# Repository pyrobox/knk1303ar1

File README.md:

# KNK1303AR1

Project of firing module of amateur pyrotechnic system. 

## Description

For many years, the forum of fireworks enthusiasts https://forumfajerwerki.pl has been implementing projects of amateur pyrotechnic systems. 
KNK1303AR1 is another project, this time compatible with the professional Pyrobox pirotechnics system, based on the Arduino Nano Every board.
The design of the pcb was created in KiCad 7.0.8 and the code for Arduino Nano Every was written in Arduino IDE 2.3.2
This module is controlled by the free Pyrobox system software downloadable from https://www.pyrobox.com.pl/soft/downloads.html

## Help

You can find more information on the forumfajerwerki.pl in the thread 
https://www.forumfajerwerki.pl/topic/9585-forumowy-projekt-opensource-systemu-pirotechnicznego/?do=findComment&comment=165880 
Forum registration is required.

A compendium of projects from the forumfajerwerki.pl
https://www.pyrobox.com.pl/knk1301/

## Authors

Zbigniew Kubicki (forumfajerwerki.pl nickname "zk1959")

## Version History

* Rev.1 as of 2024.03.10

## License

Open source hardware and freeware software.

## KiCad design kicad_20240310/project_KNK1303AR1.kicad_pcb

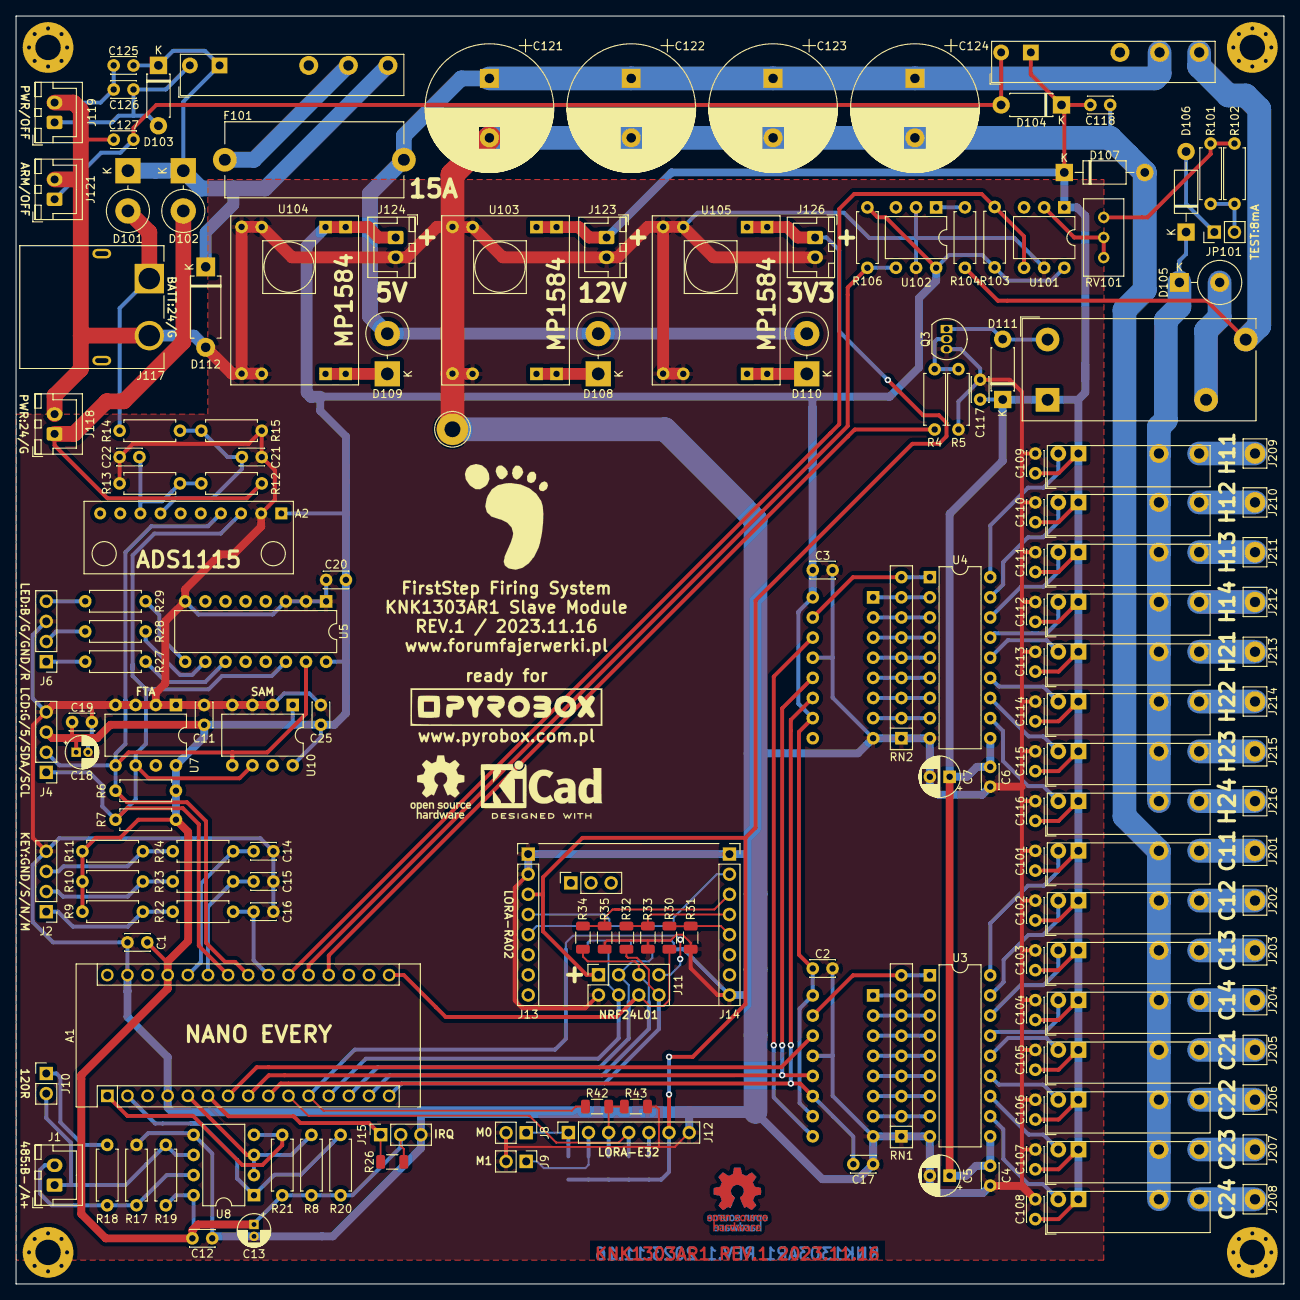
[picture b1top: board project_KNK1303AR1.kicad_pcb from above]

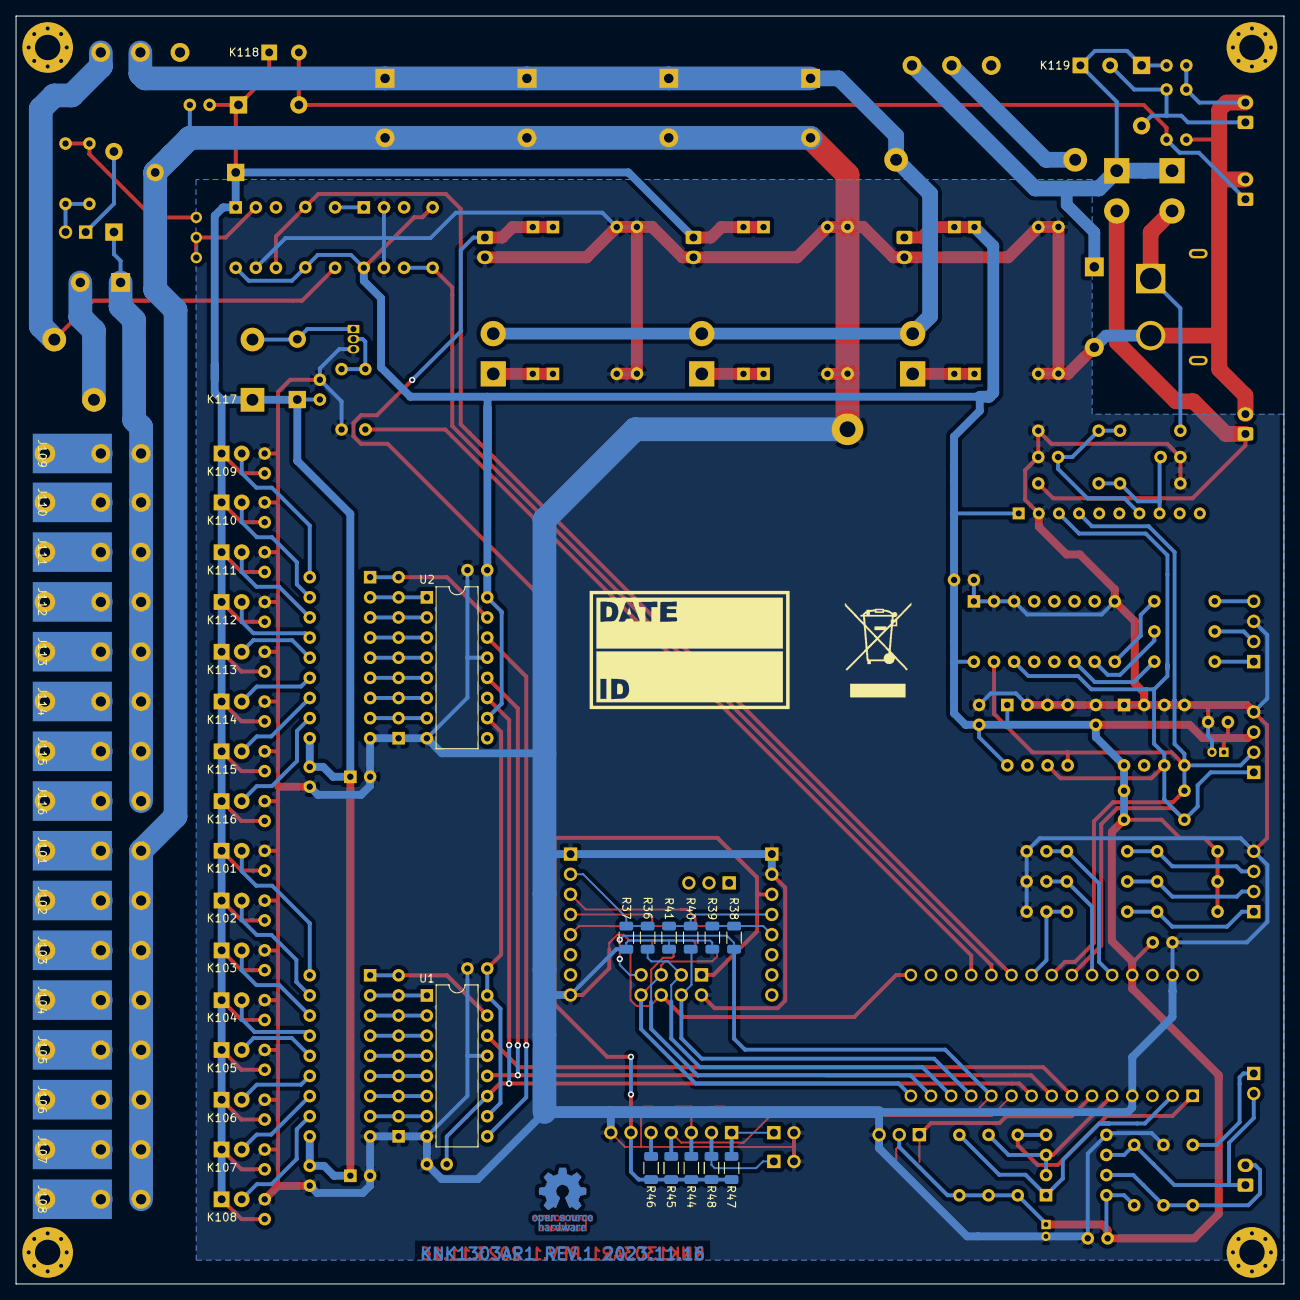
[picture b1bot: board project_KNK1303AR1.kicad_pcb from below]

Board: 2 copper layers, 160.0 x 160.0 mm, 196 parts (29 on the bottom side), 119 nets.

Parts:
A1: NANO_EVERY; Arduino_Nano
A2: ADS1115; pyrobox_module_ADC1115_mini
C1, C2, C3, C4, C6, C11, C12, C14, C15, C16, C17, C19, C20, C25, C101, C102, C103, C104, C105, C106, C107, C108, C109, C110, C111, C112, C113, C114, C115, C116, C117, C118, C125, C126, C127: 100n; C_Disc_D3.0mm_W2.0mm_P2.50mm
C5, C7: 22u; CP_Radial_D5.0mm_P2.50mm
C13, C18: 10u; CP_Radial_D4.0mm_P1.50mm
C21, C22: 150p; C_Disc_D3.0mm_W2.0mm_P2.50mm
C121, C122, C123, C124: 1K/50; CP_Radial_D16.0mm_P7.50mm
D101, D102: SB540; D_DO-201AD_P5.08mm_Vertical_KathodeUp
D103, D104, D111: 1N4148; D_DO-41_SOD81_P7.62mm_Horizontal
D105: BY550-1000; D_DO-27_P5.08mm_Vertical_KathodeUp
D106: 1N4002; D_DO-41_SOD81_P10.16mm_Horizontal
D107: 12V/1W; D_DO-41_SOD81_P10.16mm_Horizontal
D108, D109, D110: 1N5822; D_DO-201AD_P5.08mm_Vertical_KathodeUp
D112: P6KE33A; D_DO-15_P10.16mm_Horizontal
F101: 15A; Fuseholder_Cylinder-5x20mm_Stelvio-Kontek_PTF78_Horizontal_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
J1: 485; JST_XH_B2B-XH-A_1x02_P2.50mm_Vertical
J2: KEY_A; PinHeader_1x04_P2.54mm_Vertical
J4: LCD_A; PinHeader_1x04_P2.54mm_Vertical
J6: LED_A; PinHeader_1x04_P2.54mm_Vertical
J8: M0; PinHeader_1x02_P2.54mm_Vertical
J9: M1; PinHeader_1x02_P2.54mm_Vertical
J10: 120R; PinHeader_1x02_P2.54mm_Vertical
J11: NRF; PinSocket_2x04_P2.54mm_Vertical
J12: E32; PinSocket_1x07_P2.54mm_Vertical
J13: LORA_A; PinSocket_1x08_P2.54mm_Vertical
J14: LORA_B; PinSocket_1x08_P2.54mm_Vertical
J15: IRQ; PinSocket_1x03_P2.54mm_Vertical
J101: C11; SolderWirePad_1x01_SMD_5x10mm
J102: C12; SolderWirePad_1x01_SMD_5x10mm
J103: C13; SolderWirePad_1x01_SMD_5x10mm
J104: C14; SolderWirePad_1x01_SMD_5x10mm
J105: C21; SolderWirePad_1x01_SMD_5x10mm
J106: C22; SolderWirePad_1x01_SMD_5x10mm
J107: C23; SolderWirePad_1x01_SMD_5x10mm
J108: C24; SolderWirePad_1x01_SMD_5x10mm
J109: H11; SolderWirePad_1x01_SMD_5x10mm
J110: H12; SolderWirePad_1x01_SMD_5x10mm
J111: H13; SolderWirePad_1x01_SMD_5x10mm
J112: H14; SolderWirePad_1x01_SMD_5x10mm
J113: H21; SolderWirePad_1x01_SMD_5x10mm
J114: H22; SolderWirePad_1x01_SMD_5x10mm
J115: H23; SolderWirePad_1x01_SMD_5x10mm
J116: H24; SolderWirePad_1x01_SMD_5x10mm
J117: BATT_A; pyrobox_pcs_AMASS_XT60PW-M
J118: BATT2_A; JST_XH_B2B-XH-A_1x02_P2.50mm_Vertical
J119: PWR_A; JST_XH_B2B-XH-A_1x02_P2.50mm_Vertical
J121: ARM_A; JST_XH_B2B-XH-A_1x02_P2.50mm_Vertical
J123: +12V; JST_XH_B2B-XH-A_1x02_P2.50mm_Vertical
J124: +5V; JST_XH_B2B-XH-A_1x02_P2.50mm_Vertical
J126: +3V3; JST_XH_B2B-XH-A_1x02_P2.50mm_Vertical
J201: C11; Pin_D1.3mm_L10.0mm_W3.5mm_Flat
J202: C12; Pin_D1.3mm_L10.0mm_W3.5mm_Flat
J203: C13; Pin_D1.3mm_L10.0mm_W3.5mm_Flat
J204: C14; Pin_D1.3mm_L10.0mm_W3.5mm_Flat
J205: C21; Pin_D1.3mm_L10.0mm_W3.5mm_Flat
J206: C22; Pin_D1.3mm_L10.0mm_W3.5mm_Flat
J207: C23; Pin_D1.3mm_L10.0mm_W3.5mm_Flat
J208: C24; Pin_D1.3mm_L10.0mm_W3.5mm_Flat
J209: H11; Pin_D1.3mm_L10.0mm_W3.5mm_Flat
J210: H12; Pin_D1.3mm_L10.0mm_W3.5mm_Flat
J211: H13; Pin_D1.3mm_L10.0mm_W3.5mm_Flat
J212: H14; Pin_D1.3mm_L10.0mm_W3.5mm_Flat
J213: H21; Pin_D1.3mm_L10.0mm_W3.5mm_Flat
J214: H22; Pin_D1.3mm_L10.0mm_W3.5mm_Flat
J215: H23; Pin_D1.3mm_L10.0mm_W3.5mm_Flat
J216: H24; Pin_D1.3mm_L10.0mm_W3.5mm_Flat
JP101: 8mA; PinHeader_1x02_P2.54mm_Vertical
K101, K102, K103, K104, K105, K106, K107, K108, K109, K110, K111, K112, K113, K114, K115, K116: AZ921; pyrobox_pcs_ZETTLER_AZ921_vertical
K117: AZDC110; pyrobox_pcs_ZETTLER_AZDC110
K118, K119: 34.51; Relay_SPDT_Finder_34.51_Vertical
Q3: BC547; TO-92_Inline
R4, R6, R7, R9, R10, R11: 10K; R_Axial_DIN0207_L6.3mm_D2.5mm_P7.62mm_Horizontal
R5, R8, R17, R19, R20, R21: 4K7; R_Axial_DIN0207_L6.3mm_D2.5mm_P7.62mm_Horizontal
R12, R14: 15K/1%; R_Axial_DIN0207_L6.3mm_D2.5mm_P7.62mm_Horizontal
R13, R15: 3K/1%; R_Axial_DIN0207_L6.3mm_D2.5mm_P7.62mm_Horizontal
R18, R29: 120R; R_Axial_DIN0207_L6.3mm_D2.5mm_P7.62mm_Horizontal
R22, R23, R24: 100R; R_Axial_DIN0207_L6.3mm_D2.5mm_P7.62mm_Horizontal
R26, R44, R45, R46, R47, R48: 4K7; R_1206_3216Metric
R27: 200R; R_Axial_DIN0207_L6.3mm_D2.5mm_P7.62mm_Horizontal
R28: 180R; R_Axial_DIN0207_L6.3mm_D2.5mm_P7.62mm_Horizontal
R30, R32, R34, R36, R38, R40, R42: 220R; R_1206_3216Metric
R31, R33, R35, R37, R39, R41, R43: 470R; R_1206_3216Metric
R101, R102: 2K2; R_Axial_DIN0207_L6.3mm_D2.5mm_P7.62mm_Horizontal
R103, R106: 270R; R_Axial_DIN0207_L6.3mm_D2.5mm_P7.62mm_Horizontal
R104: 2K4; R_Axial_DIN0207_L6.3mm_D2.5mm_P7.62mm_Horizontal
RN1, RN2: 1K; R_Array_SIP9
RV101: 1K; zk_Bourns_3386C_Horizontal
U1, U2: 74HC595; DIP-16_W7.62mm
U3, U4: ULN2803A; DIP-18_W7.62mm
U5: PCF8574A; DIP-16_W7.62mm
U7, U10: 24LC256; DIP-8_W7.62mm
U8: MAX485EPA+; DIP-8_W7.62mm
U101, U102: H11L3; DIP-6_W7.62mm
U103: MP1584_12V; pyrobox_module_MP1584EN_2
U104: MP1584_5V; pyrobox_module_MP1584EN_2
U105: MP1584_3V3; pyrobox_module_MP1584EN_2

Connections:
+3V3: J11.1, J12.6, J13.3, J126.1, R44.2, R45.2, R46.2, R47.2, R48.2, U105.3
+5V: A1.27, A2.1, C1.1, C2.1, C3.1, C11.1, C12.1, C13.1, C18.1, C19.1, C20.1, C25.1, J4.3, J15.2, J124.1, R6.1, R7.2, R8.2, R9.2, R10.2, R11.2, R19.1, R20.2, R21.2, R26.2, R103.2, R106.2, U1.10, U1.16, U2.10, U2.16, U5.16, U7.8, U8.8, U10.1, U10.8, U101.6, U102.6, U104.3
+12V: C4.1, C5.1, C6.1, C7.1, C101.2, C102.2, C103.2, C104.2, C105.2, C106.2, C107.2, C108.2, C109.2, C110.2, C111.2, C112.2, C113.2, C114.2, C115.2, C116.2, C117.2, C118.2, D104.1, D107.1, D111.1, J123.1, K101.A1, K102.A1, K103.A1, K104.A1, K105.A1, K106.A1, K107.A1, K108.A1, K109.A1, K110.A1, K111.A1, K112.A1, K113.A1, K114.A1, K115.A1, K116.A1, K117.A1, K118.A1, U3.10, U4.10, U101.1, U103.3
/sheet_KNK1303AR1_01/485_DIR: A1.5, R8.1, U8.2, U8.3
/sheet_KNK1303AR1_01/485_RX: A1.2, R20.1, U8.1
/sheet_KNK1303AR1_01/485_TX: A1.1, R21.1, U8.4
/sheet_KNK1303AR1_01/595_CLOCK: A1.9, C17.1, U1.11, U2.11
/sheet_KNK1303AR1_01/595_DATA: A1.7, U1.14
/sheet_KNK1303AR1_01/595_LATCH: A1.8, U1.12, U2.12
/sheet_KNK1303AR1_01/I2C_SCL: A1.24, A2.3, J4.1, R7.1, U5.14, U7.6, U10.6
/sheet_KNK1303AR1_01/I2C_SDA: A1.23, A2.4, J4.2, R6.2, U5.15, U7.5, U10.5
/sheet_KNK1303AR1_01/INT0: A1.6, J15.1, R26.1
/sheet_KNK1303AR1_01/OUT_FR: A1.19, R4.1
/sheet_KNK1303AR1_01/SPI_CE: A1.12, J11.4, R40.1
/sheet_KNK1303AR1_01/SPI_CS: A1.13, J11.3, R36.1
/sheet_KNK1303AR1_01/SPI_IRQ: A1.11, J11.7, R38.1, R42.1
/sheet_KNK1303AR1_01/SPI_MISO: A1.15, J11.8, R32.1
/sheet_KNK1303AR1_01/SPI_MOSI: A1.14, J11.5, R34.1
/sheet_KNK1303AR1_01/SPI_NC: A1.10, J12.4, R45.1
/sheet_KNK1303AR1_01/SPI_SCK: A1.16, J11.6, R30.1
/sheet_KNK1303AR1_01/SW_MENU: A1.22, C16.1, R22.1
/sheet_KNK1303AR1_01/SW_NEXT: A1.25, C15.1, R23.1
/sheet_KNK1303AR1_01/SW_SET: A1.26, C14.1, R24.1
/sheet_KNK1303AR1_02/PWR_25: C121.1, C122.1, C123.1, C124.1, D108.2, D109.2, D110.2, F101.1, K118.11
GND: A1.4, A1.29, A2.2, C1.2, C2.2, C3.2, C4.2, C5.2, C6.2, C7.2, C11.2, C12.2, C13.2, C14.2, C15.2, C16.2, C17.2, C18.2, C19.2, C20.2, C21.2, C22.2, C25.2, C101.1, C102.1, C103.1, C104.1, C105.1, C106.1, C107.1, C108.1, C109.1, C110.1, C111.1, C112.1, C113.1, C114.1, C115.1, C116.1, C117.1, C118.1, C121.2, C122.2, C123.2, C124.2, C125.1, C126.2, C127.2, D107.2, D112.2, J2.4, J4.4, J6.3, J8.2, J9.2, J11.2, J12.7, J13.1, J13.2, J14.1, J14.8, J15.3, J117.2, J118.2, J119.2, J121.2, J123.2, J124.2, J126.2, K101.11, K102.11, K103.11, K104.11, K105.11, K106.11, K107.11, K108.11, Q3.3, R5.1, R13.1, R15.1, R17.1, R31.1, R33.1, R35.1, R37.1, R39.1, R41.1, R43.1, RN1.1, RN2.1, U1.8, U1.13, U2.8, U2.13, U3.9, U4.9, U5.1, U5.2, U5.3, U5.8, U7.1, U7.2, U7.3, U7.4, U8.5, U10.2, U10.3, U10.4, U101.5, U102.2, U102.5, U103.2, U103.4, U104.2, U104.4, U105.2, U105.4
IN_ARM: A1.20, R106.1, U102.4
IN_PWR1: D101.2, J117.1, R14.2
IN_PWR2: D102.2, J118.1, R12.1
IN_TEST: A1.21, R103.1, U101.4
unnamed: A2.7, C21.1, R14.1, R15.2
unnamed: A2.8, C22.1, R12.2, R13.2
unnamed: C125.2, D101.1, D102.1, D103.1, D112.1, K119.14, K119.A1
unnamed: C126.1, D103.2, J119.1, K119.A2
unnamed: C127.1, D104.2, J121.1, K118.A2
unnamed: D105.1, D106.1, K109.11, K110.11, K111.11, K112.11, K113.11, K114.11, K115.11, K116.11
unnamed: D105.2, K117.11
unnamed: D106.2, JP101.1
unnamed: D108.1, U103.1
unnamed: D109.1, U104.1
unnamed: D110.1, U105.1
unnamed: F101.2, K119.11
unnamed: J1.1, J10.2, R19.2, U8.6
unnamed: J1.2, R17.2, R18.1, U8.7
unnamed: J2.1, R9.1, R22.2
unnamed: J2.2, R10.1, R23.2
unnamed: J2.3, R11.1, R24.2
unnamed: J6.1, R27.1
unnamed: J6.2, R28.1
unnamed: J6.4, R29.1
unnamed: J10.1, R18.2
unnamed: J8.1, J12.1, R47.1
unnamed: J9.1, J12.2, R48.1
unnamed: J12.3, R42.2, R43.2, R44.1
unnamed: J12.5, R46.1
unnamed: J13.4, R40.2, R41.2
unnamed: J13.5, R38.2, R39.2
unnamed: J14.2, R36.2, R37.2
unnamed: J14.3, R34.2, R35.2
unnamed: J14.4, R32.2, R33.2
unnamed: J14.5, R30.2, R31.2
unnamed: J101.1, J201.1, K101.14
unnamed: J102.1, J202.1, K102.14
unnamed: J103.1, J203.1, K103.14
unnamed: J104.1, J204.1, K104.14
unnamed: J105.1, J205.1, K105.14
unnamed: J106.1, J206.1, K106.14
unnamed: J107.1, J207.1, K107.14
unnamed: J108.1, J208.1, K108.14
unnamed: J109.1, J209.1, K109.14
unnamed: J110.1, J210.1, K110.14
unnamed: J111.1, J211.1, K111.14
unnamed: J112.1, J212.1, K112.14
unnamed: J113.1, J213.1, K113.14
unnamed: J114.1, J214.1, K114.14
unnamed: J115.1, J215.1, K115.14
unnamed: J116.1, J216.1, K116.14
unnamed: JP101.2, R101.1, R102.1
unnamed: K117.14, K118.14, R104.1
unnamed: Q3.2, R4.2, R5.2
unnamed: R27.2, U5.11
unnamed: R28.2, U5.10
unnamed: R29.2, U5.9
unnamed: R101.2, R102.2, RV101.1
unnamed: R104.2, U102.1
unnamed: RN1.2, U1.7, U3.8
unnamed: RN1.3, U1.6, U3.7
unnamed: RN1.4, U1.5, U3.6
unnamed: RN1.5, U1.4, U3.5
unnamed: RN1.6, U1.3, U3.4
unnamed: RN1.7, U1.2, U3.3
unnamed: RN1.8, U1.1, U3.2
unnamed: RN1.9, U1.15, U3.1
unnamed: RN2.2, U2.7, U4.8
unnamed: RN2.3, U2.6, U4.7
unnamed: RN2.4, U2.5, U4.6
unnamed: RN2.5, U2.4, U4.5
unnamed: RN2.6, U2.3, U4.4
unnamed: RN2.7, U2.2, U4.3
unnamed: RN2.8, U2.1, U4.2
unnamed: RN2.9, U2.15, U4.1
unnamed: RV101.2, RV101.3, U101.2
unnamed: U1.9, U2.14
OUT_C11: K101.A2, U3.18
OUT_C12: K102.A2, U3.17
OUT_C13: K103.A2, U3.16
OUT_C14: K104.A2, U3.15
OUT_C21: K105.A2, U3.14
OUT_C22: K106.A2, U3.13
OUT_C23: K107.A2, U3.12
OUT_C24: K108.A2, U3.11
OUT_FIRE: D111.2, K117.A2, Q3.1
OUT_H11: K109.A2, U4.18
OUT_H12: K110.A2, U4.17
OUT_H13: K111.A2, U4.16
OUT_H14: K112.A2, U4.15
OUT_H21: K113.A2, U4.14
OUT_H22: K114.A2, U4.13
OUT_H23: K115.A2, U4.12
OUT_H24: K116.A2, U4.11

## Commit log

2024-03-25 kicad_20240310 files added
2024-03-25 kicad_20240310.zip file added
2024-03-28 add new readme.md
2024-03-28 img_20240310 files added
2024-03-29 arduino_20240310.zip file added
2024-03-29 arduino_20240310 files added
2024-03-29 pbm_711412 files added
